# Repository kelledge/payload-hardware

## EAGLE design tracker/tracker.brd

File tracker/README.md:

Bill of Materials
-----------------

http://www.digikey.com/product-detail/en/XBP9B-DPST-001/602-1349-ND/3594160
http://www.digikey.com/product-detail/en/XBP9B-DPUT-001/602-1350-ND/3594161

Reference Documents
-------------------

http://electronics.stackexchange.com/questions/36930/some-advice-on-charging-circuit-used-in-simple-ups/36938#36938

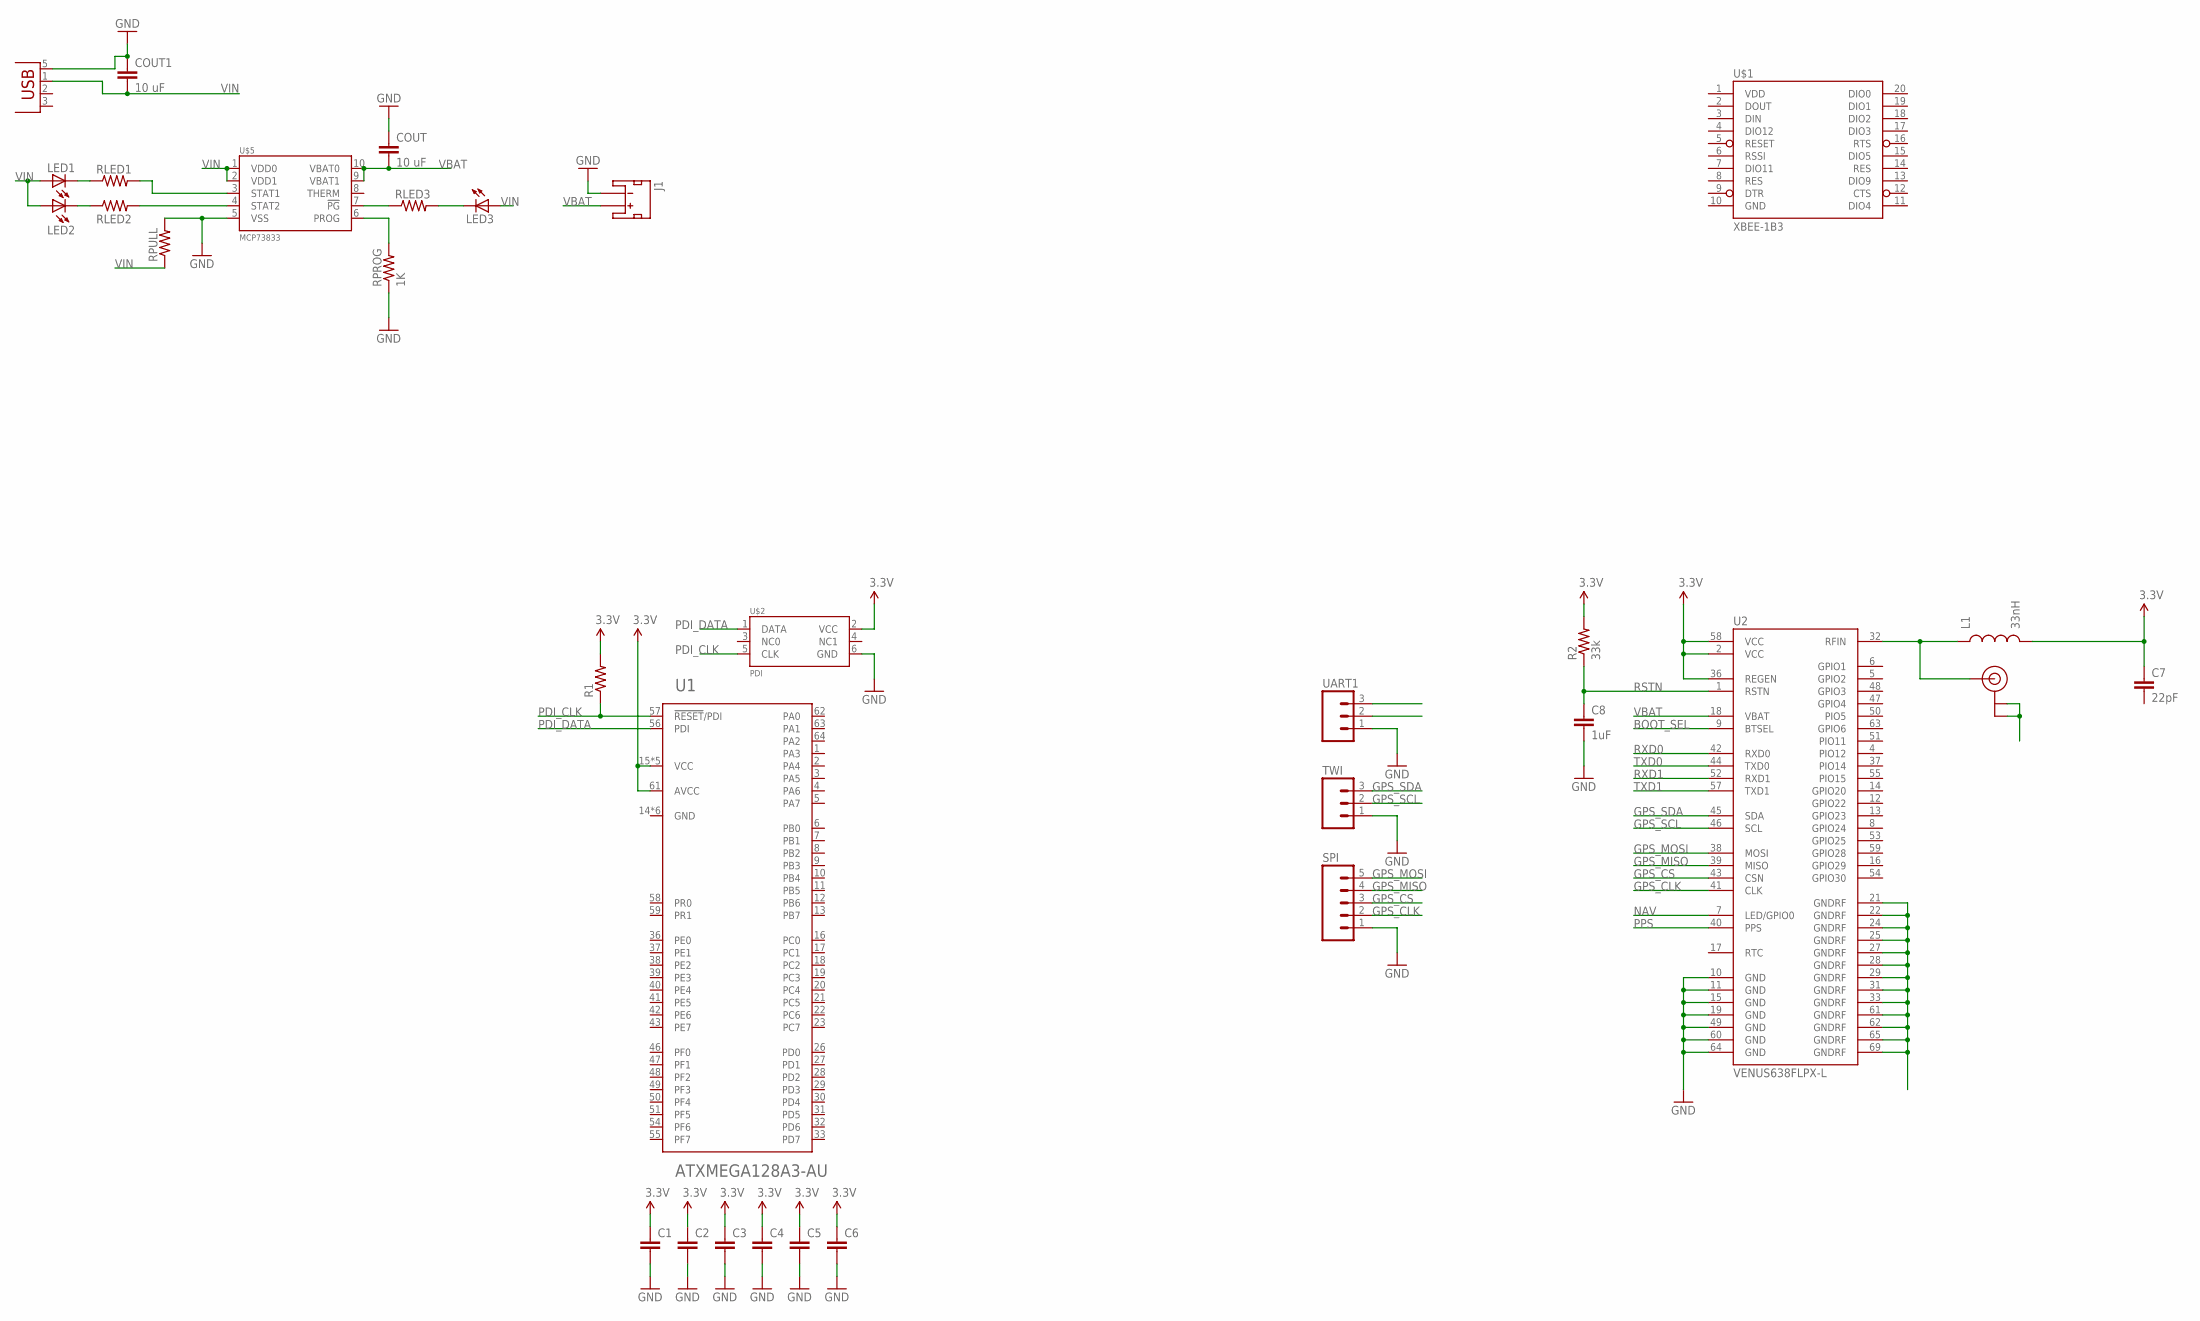
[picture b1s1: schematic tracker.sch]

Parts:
C1, C2, C3, C4, C5, C6: CAP0805; 0805
C7: 22pF; 0805
C8: 1uF; 0805
COUT, COUT1: 10 uF; 0805
J1: JST_2MM_MALE; JST-2-SMD
L1: 33nH; 0805
LED1, LED2, LED3: LEDCHIP-LED0805; CHIP-LED0805
R1: RESISTOR0805-RES; 0805
R2: 33k; 0805
RLED1, RLED2, RLED3: RESISTOR0805-RES; 0805
RPROG: 1K; 0805
RPULL: RESISTOR0805-RES; 0805
SPI: M05PTH; 1X05
TWI: M03PTH; 1X03
U1: ATXMEGA128A3-AU; TQFP-64A-64
U2: VENUS638FLPX-L; VENUS638FLPX
U$1: XBEE-1B3; XBEE-SMD
U$2: PDI; 2X3
U$3: SL1204
U$4: USB; USB_MICRO_B
U$5: MCP73833; MSOP10
UART1: M03PTH; 1X03

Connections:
3.3V: C1.1, C2.1, C3.1, C4.1, C5.1, C6.1, C7.1, L1.2, R1.2, R2.2, U1.15 (VCC), U1.25 (VCC), U1.35 (VCC), U1.45 (VCC), U1.53 (VCC), U1.61 (AVCC), U2.2 (VCC), U2.36 (REGEN), U2.58 (VCC), U$2.2 (VCC)
BOOT_SEL: U2.9 (BTSEL)
GND: C1.2, C2.2, C3.2, C4.2, C5.2, C6.2, C8.2, COUT.1, COUT1.1, J1.1 (-), RPROG.1, RPULL.2, SPI.1, TWI.1, U1.14 (GND), U1.24 (GND), U1.34 (GND), U1.44 (GND), U1.52 (GND), U1.60 (GND), U2.10 (GND), U2.11 (GND), U2.15 (GND), U2.19 (GND), U2.49 (GND), U2.60 (GND), U2.64 (GND), U$1.10 (GND), U$2.6 (GND), U$4.5 (GND), U$5.5 (VSS), UART1.1
GPS_CLK: SPI.2, U2.41 (CLK)
GPS_CS: SPI.3, U2.43 (CSN)
GPS_MISO: SPI.4, U2.39 (MISO)
GPS_MOSI: SPI.5, U2.38 (MOSI)
GPS_SCL: TWI.2, U2.46 (SCL)
GPS_SDA: TWI.3, U2.45 (SDA)
unnamed: U2.21 (GNDRF), U2.22 (GNDRF), U2.24 (GNDRF), U2.25 (GNDRF), U2.27 (GNDRF), U2.28 (GNDRF), U2.29 (GNDRF), U2.31 (GNDRF), U2.33 (GNDRF), U2.61 (GNDRF), U2.62 (GNDRF), U2.65 (GNDRF), U2.69 (GNDRF)
unnamed: RLED3.1, U$5.7 (!PG)
unnamed: RLED2.2, U$5.4 (STAT2)
unnamed: RLED1.2, U$5.3 (STAT1)
unnamed: LED1.C, RLED1.1
unnamed: LED2.C, RLED2.1
unnamed: LED3.C, RLED3.2
unnamed: L1.1, U2.32 (RFIN), U$3.2 (SIGNAL)
unnamed: U$3.1 (GND), U$3.3 (GND)
unnamed: RPROG.2, U$5.6 (PROG)
NAV: U2.7 (LED/GPIO0)
PDI_CLK: R1.1, U1.57 (!RESET!/PDI), U$2.5 (CLK)
PDI_DATA: U1.56 (PDI), U$2.1 (DATA)
PPS: U2.40 (PPS)
RSTN: C8.1, R2.1, U2.1 (RSTN)
RXD0: U2.42 (RXD0)
RXD1: U2.52 (RXD1)
TXD0: U2.44 (TXD0)
TXD1: U2.57 (TXD1)
VBAT: COUT.2, J1.2 (+), U2.18 (VBAT), U$5.9 (VBAT1), U$5.10 (VBAT0)
VDD: U$1.1 (VDD)
VIN: COUT1.2, LED1.A, LED2.A, LED3.A, RPULL.1, U$4.1 (VBUS), U$5.1 (VDD0), U$5.2 (VDD1)

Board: 2 copper layers, 32 parts (1 on the bottom side), 23 nets, no tracks yet.

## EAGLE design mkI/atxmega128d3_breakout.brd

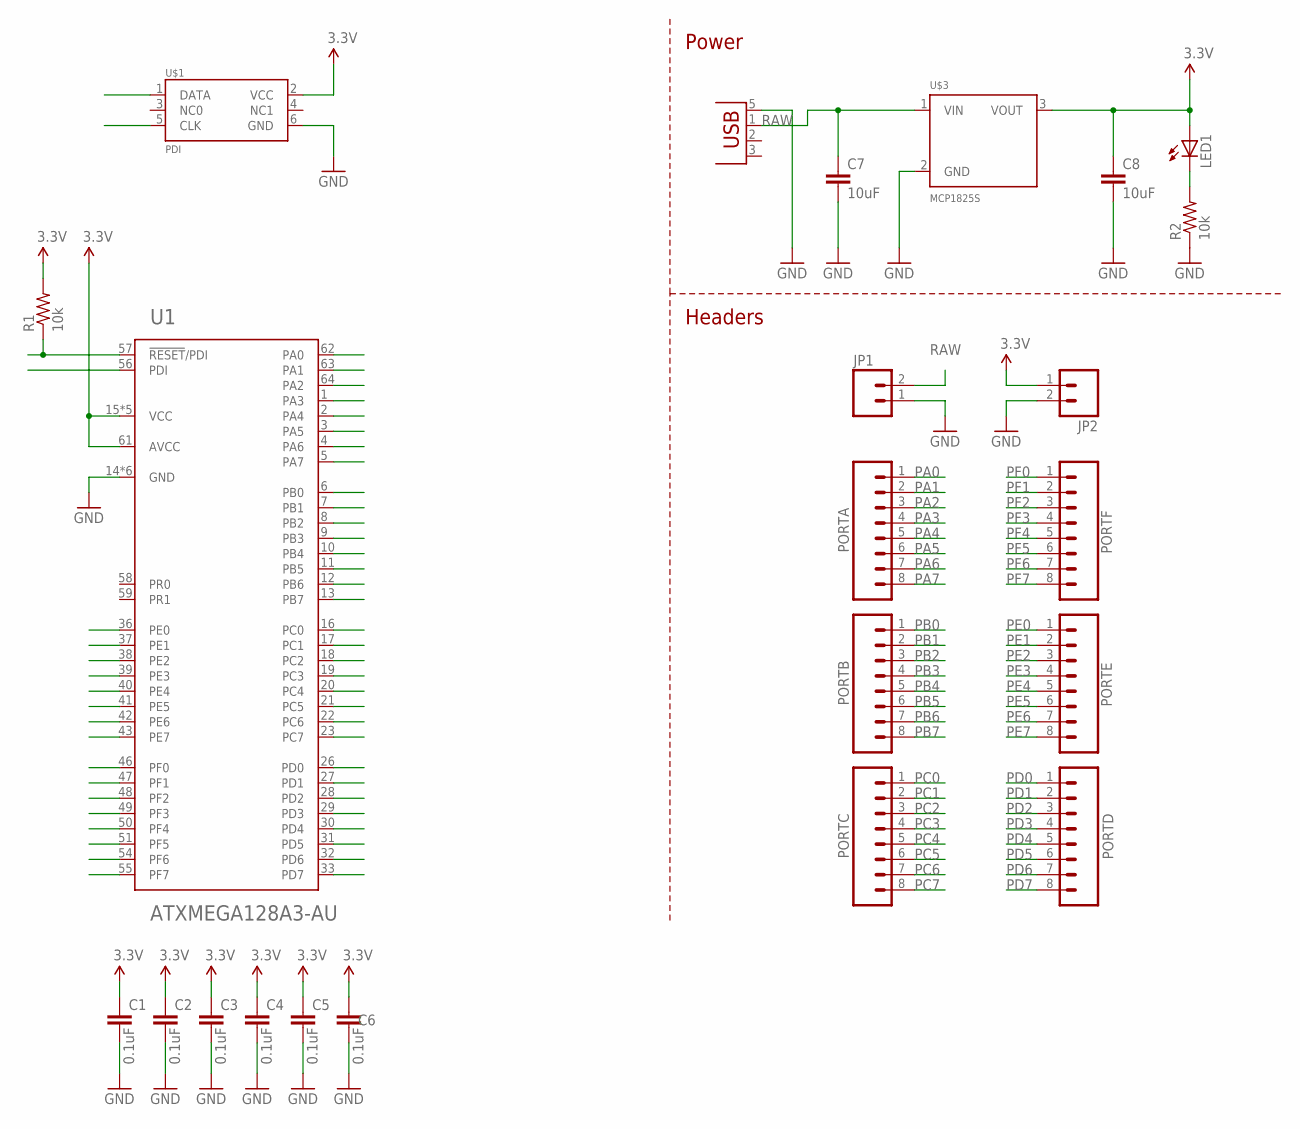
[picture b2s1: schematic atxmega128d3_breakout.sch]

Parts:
C1, C2, C3, C4, C5, C6: 0.1uF; 0805
C7, C8: 10uF; 0805
JP1, JP2: M02PTH; 1X02
LED1: LEDCHIP-LED0805; CHIP-LED0805
PORTA: M081X08; 1X08
PORTB: M081X08; 1X08
PORTC: M081X08; 1X08
PORTD: M081X08; 1X08
PORTE: M081X08; 1X08
PORTF: M081X08; 1X08
R1, R2: 10k; 0805
U1: ATXMEGA128A3-AU; TQFP-64A-64
U$1: PDI; 2X3
U$2: USB; USB_MICRO_B
U$3: MCP1825S; SOT233

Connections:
3.3V: C1.1, C2.1, C3.1, C4.1, C5.1, C6.1, C8.1, JP2.1, LED1.A, R1.2, U1.15 (VCC), U1.25 (VCC), U1.35 (VCC), U1.45 (VCC), U1.53 (VCC), U1.61 (AVCC), U$1.2 (VCC), U$3.3 (VOUT)
CLK: R1.1, U1.57 (!RESET!/PDI), U$1.5 (CLK)
DATA: U1.56 (PDI), U$1.1 (DATA)
GND: C1.2, C2.2, C3.2, C4.2, C5.2, C6.2, C7.2, C8.2, JP1.1, JP2.2, R2.1, U1.14 (GND), U1.24 (GND), U1.34 (GND), U1.44 (GND), U1.52 (GND), U1.60 (GND), U$1.6 (GND), U$2.5 (GND), U$3.2 (GND)
unnamed: LED1.C, R2.2
PA0: PORTA.1, U1.62 (PA0)
PA1: PORTA.2, U1.63 (PA1)
PA2: PORTA.3, U1.64 (PA2)
PA3: PORTA.4, U1.1 (PA3)
PA4: PORTA.5, U1.2 (PA4)
PA5: PORTA.6, U1.3 (PA5)
PA6: PORTA.7, U1.4 (PA6)
PA7: PORTA.8, U1.5 (PA7)
PB0: PORTB.1, U1.6 (PB0)
PB1: PORTB.2, U1.7 (PB1)
PB2: PORTB.3, U1.8 (PB2)
PB3: PORTB.4, U1.9 (PB3)
PB4: PORTB.5, U1.10 (PB4)
PB5: PORTB.6, U1.11 (PB5)
PB6: PORTB.7, U1.12 (PB6)
PB7: PORTB.8, U1.13 (PB7)
PC0: PORTC.1, U1.16 (PC0)
PC1: PORTC.2, U1.17 (PC1)
PC2: PORTC.3, U1.18 (PC2)
PC3: PORTC.4, U1.19 (PC3)
PC4: PORTC.5, U1.20 (PC4)
PC5: PORTC.6, U1.21 (PC5)
PC6: PORTC.7, U1.22 (PC6)
PC7: PORTC.8, U1.23 (PC7)
PD0: PORTD.1, U1.26 (PD0)
PD1: PORTD.2, U1.27 (PD1)
PD2: PORTD.3, U1.28 (PD2)
PD3: PORTD.4, U1.29 (PD3)
PD4: PORTD.5, U1.30 (PD4)
PD5: PORTD.6, U1.31 (PD5)
PD6: PORTD.7, U1.32 (PD6)
PD7: PORTD.8, U1.33 (PD7)
PE0: PORTE.1, U1.36 (PE0)
PE1: PORTE.2, U1.37 (PE1)
PE2: PORTE.3, U1.38 (PE2)
PE3: PORTE.4, U1.39 (PE3)
PE4: PORTE.5, U1.40 (PE4)
PE5: PORTE.6, U1.41 (PE5)
PE6: PORTE.7, U1.42 (PE6)
PE7: PORTE.8, U1.43 (PE7)
PF0: PORTF.1, U1.46 (PF0)
PF1: PORTF.2, U1.47 (PF1)
PF2: PORTF.3, U1.48 (PF2)
PF3: PORTF.4, U1.49 (PF3)
PF4: PORTF.5, U1.50 (PF4)
PF5: PORTF.6, U1.51 (PF5)
PF6: PORTF.7, U1.54 (PF6)
PF7: PORTF.8, U1.55 (PF7)
RAW: C7.1, JP1.2, U$2.1 (VBUS), U$3.1 (VIN)

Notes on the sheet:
Headers
Power

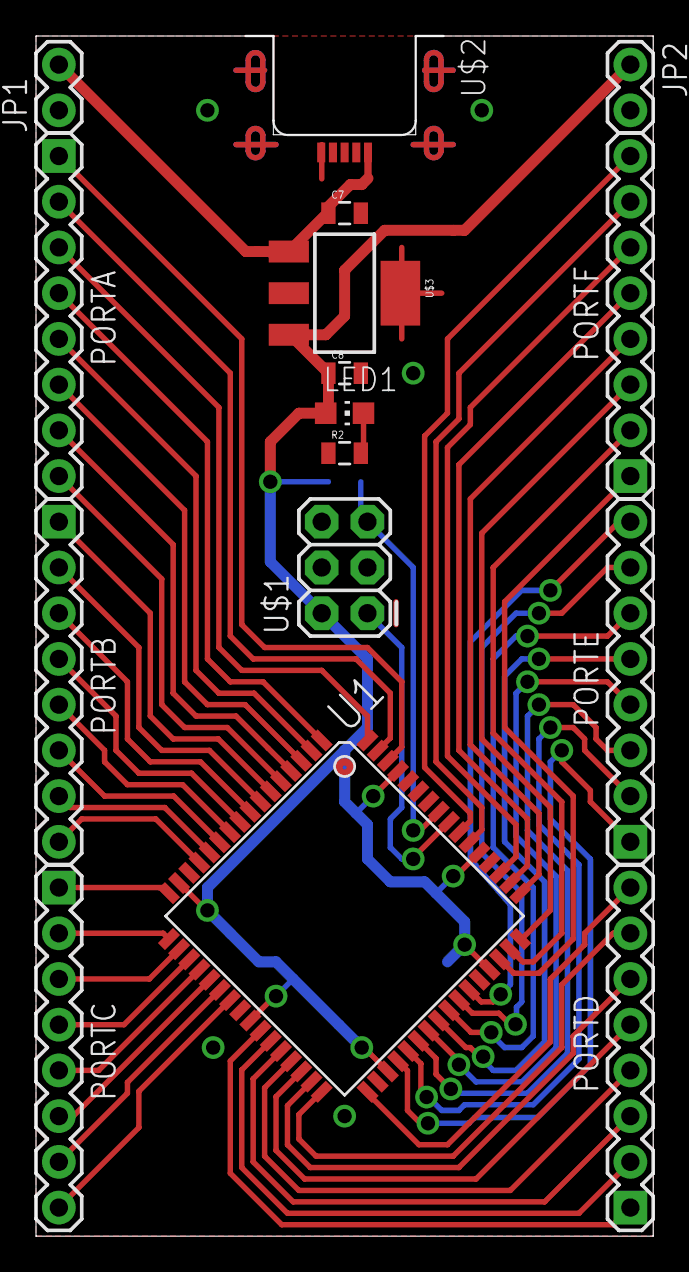
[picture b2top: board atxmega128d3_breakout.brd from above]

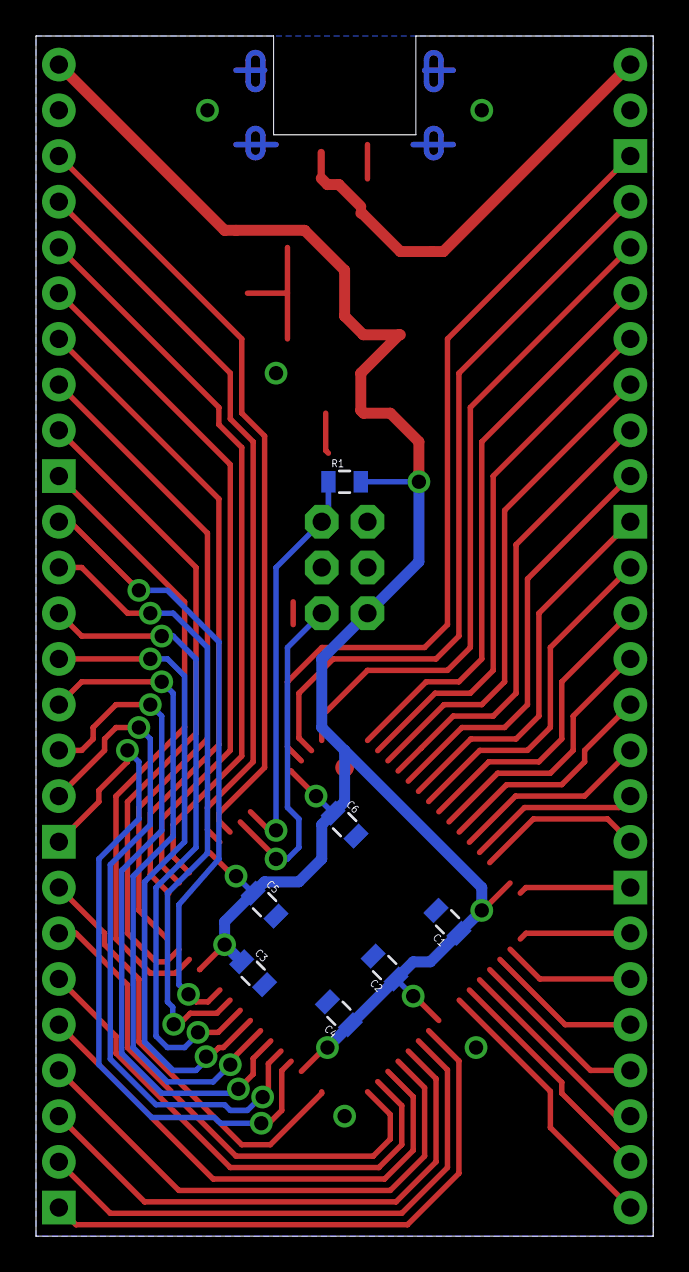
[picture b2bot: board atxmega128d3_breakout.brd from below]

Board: 2 copper layers, 34.3 x 66.7 mm, 23 parts (7 on the bottom side), 54 nets.

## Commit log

2013-03-01 inital commit
2013-04-24 pdf output of board and schematic
2013-10-05 added GPS helix antenna
2013-10-05 initial work on tracker GPS hardware
2013-10-05 git ignore added
2014-02-15 initial import of BOM
    * will be populated as parts are selected
2014-02-15 xmega now connected to pdi connector
2014-02-22 Started adding components to BOM
    I'm not sure which XBee Kevin was looking at.
2014-02-25 Added a couple more components.
    I think most of the components are listed, we just need to discuss what
    products to use in those roles.
2014-03-04 Added Components
    I added resistors, capacitors, and headers.
2014-03-15 README and docs
    * README.md added
    * docs subfolder for datasheets
2014-03-15 more docs
2014-03-15 added the MCP73833
    * The MCP73833 from Microchip has been added.
    This device is a stand-alone li-ion li-po charging solution.
2014-03-15 initial steps for the charging/power circuit
    * micro usb port added
    * 2-pin jst battery connector added
2014-03-15 reference section added
2014-03-15 Initial power connection
    * Added charging IC
2014-04-05 Updates to charging circuit
    * completed all connections for the charging circuit, except the
    thermistor as it is still undecided how we will deal with that.
    * still need to choose a voltage regulator and add it between the
    battery and main circuit.
2014-04-29 Added document
    Added document for shocky diode, transistor chip

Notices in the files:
parts and their libraries:
SparkFun: Licensing: CC v3.0 Share-Alike You are welcome to use this library for commercial purposes.
SparkFun-Connectors: Licensing: Creative Commons ShareAlike 4.0 International - https://creativecommons.org/licenses/by-sa/4.0
